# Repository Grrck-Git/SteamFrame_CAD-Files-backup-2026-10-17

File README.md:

# Steam Frame Hardware Reference

> [!WARNING]
> Information provided within this repository is for informational purposes only. The reference material is provided on an AS-IS basis. Valve Corporation reserves the right to change hardware designs in any way. Valve is not responsible for any damage to hardware that may arise from the use of mechanical or electrical interfaces to the Steam Frame that are not "Steam Frame Compatible."  This includes opening or making modifications to the Steam Frame. Content provided in this repository may not be used for commercial purposes. If you wish to pursue a commercial license please reach out to us at steamframecompatible at valvesoftware com.  Please refer to the license.txt document in this repository for all terms and conditions.

This repo contains:
1. Documents for interfacing to the expansion port. **Please read all warnings if designing your own hardware to interface to the expansion port.** This is in the [documents-expansion-port](documents-expansion-port/) folder. 
2. Stripped down CAD of the core module, in the [documents-coremodule](documents-coremodule/) folder.
3. A full USB 3.0 Hub example, built in Altium, found in the [example-expansion-port-full-usb-3.0](example-expansion-port-full-usb-3.0/) folder.
4. A minimal USB 3.0 Hub example, built in KiCad, found in the [example-expansion-port-short-usb](example-expansion-port-short-usb/)
5. Stripped down CAD of the headstrap, in the [documents-headstrap](documents-headstrap/) folder.
6. LED Locations for the controllers in [documents-controller/Steam_Frame_Controller_LED_Locations](documents-controller/Steam_Frame_Controller_LED_Locations.pdf)
7. Controller CAD in [documents-controller](documents-controller)

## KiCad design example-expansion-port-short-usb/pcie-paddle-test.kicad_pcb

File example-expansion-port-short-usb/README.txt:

This is a minimal example for using the expansion port.  We do not recommend using this for a real accessory, because of the rigid connection to the expansion port. But, it is a minimal reference for what could be done to interface with the expansion port.

Could install 1mm headers on top or bottom.

COPPER TOP side FACES USER 

Use:
 * 0.2mm holes
 * 0.1mm outside precision

REQUIREMENTS:
 * ENIG (prefer 2u) or Hard gold pads.
 * 0.8mm total thickness

Custom Notes:
 * You MUST chamfer edge connector.

IF NOT CHAMFERING:
 * 5x3 Panelization
 * Rails All 4 Sides
 * V-Cuts
 * 2mm Spacing between top and bottom.

IF CHAMFERING:
 * 5x2 Panelization
 * Rails All 4 Sides
 * V-Cuts
 * 2mm Spacing between top and bottom.

KiKit Recommended Configuration:
```json
{
    "layout": {
        "alternation": "rows",
        "vspace": "25mm",
        "vbonefirst": "2",
        "rows": "2",
        "cols": "5"
    },
    "cuts": {
        "type": "mousebites"
    },
    "framing": {
        "type": "railslr"
    }
}
```

```
kikit panelize^
    --layout "alternation: rows; vspace: 25mm; hbonefirst: 2; rotation: 180deg; rows: 2; cols: 5" ^
    --tabs "vwidth: 4.7mm; hwidth: 5mm; spacing: 15mm" ^
    --cuts "type: vcuts" ^
    --framing "type: railslr" ^
    "pcie-paddle-test.kicad_pcb" "outd.kicad_pcb"

```

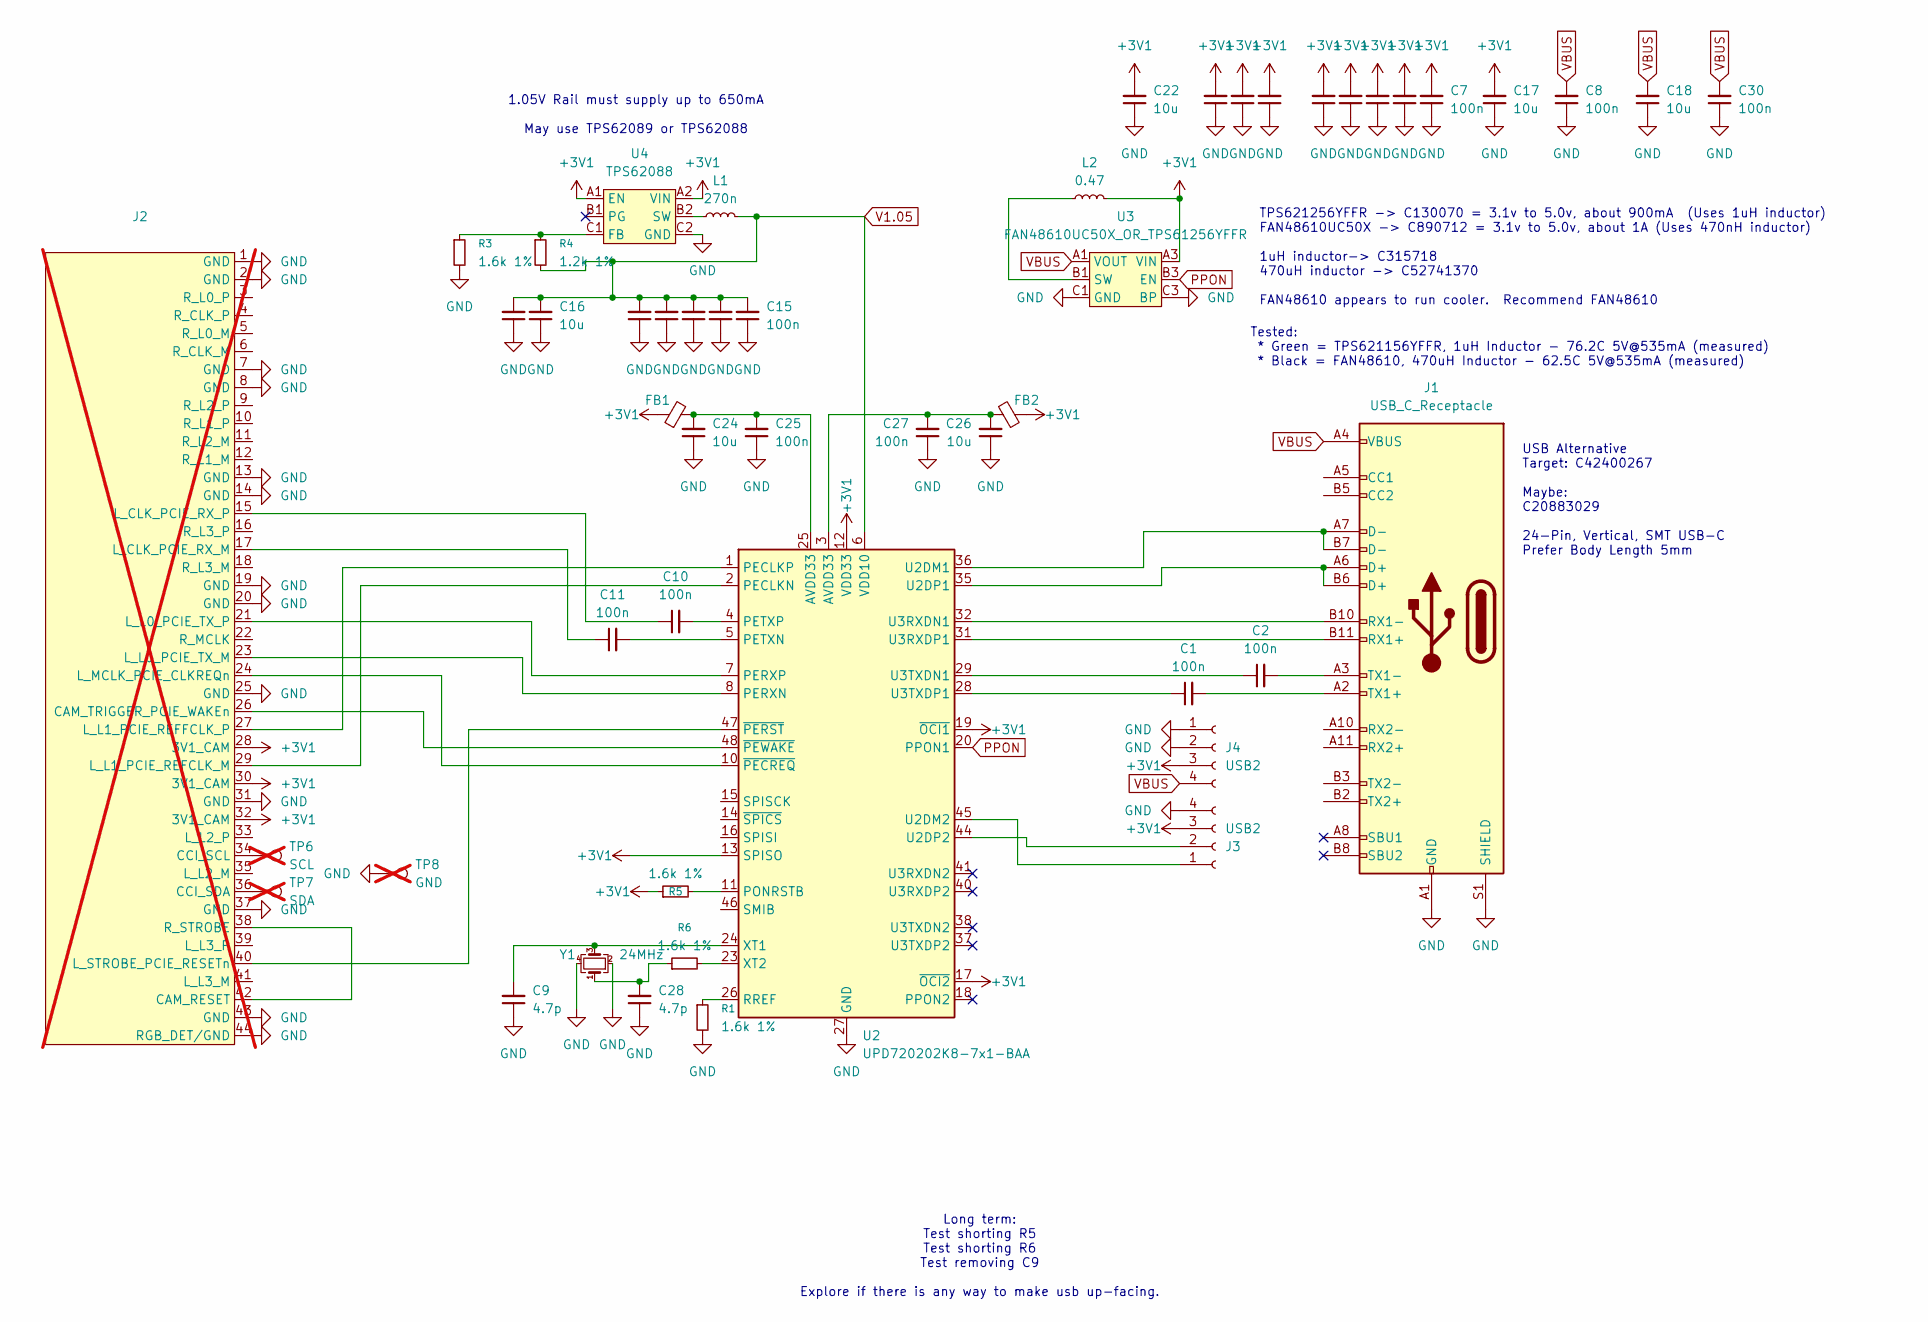
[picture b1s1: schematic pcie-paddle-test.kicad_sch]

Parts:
C1, C2, C3, C4, C5, C6, C7, C8, C10, C11, C12, C13, C14, C15, C19, C20, C23, C25, C27, C29, C30: 100n; C_0201_0603Metric; LCSC C52033358
C9, C28: 4.7p; C_0201_0603Metric; LCSC C255351
C16, C17, C18, C21, C22, C24, C26: 10u; C_0402_1005Metric; LCSC C315248
FB1, FB2: FerriteBead_Small; L_0201_0603Metric; LCSC C710325
J1: USB_C_Receptacle; USB_C_Receptacle_GCT_USB4115-03-C; LCSC C20883029
J2: PCIE-PADDLE-NO-NECK; not fitted
J3, J4: USB2; PinHeader_1x04_P1.00mm_Vertical; LCSC C22465687
L1: 270n; L_0603_1608Metric; LCSC C2041707
L2: 0.47; L_0805_2012Metric; LCSC C52741370
R1, R3, R5, R6: 1.6k 1%; R_0201_0603Metric; LCSC C295784
R4: 1.2k 1%; R_0201_0603Metric; LCSC C327393
TP6: SCL; TestPoint_Pad_D1.0mm; not fitted
TP7: SDA; TestPoint_Pad_D1.0mm; not fitted
TP8: GND; TestPoint_Pad_D1.0mm; not fitted
U2: UPD720202K8-7x1-BAA; QFN-48-1EP_7x7mm_P0.5mm_EP5.7x5.7mm; LCSC C2916548
U3: FAN48610UC50X_OR_TPS61256YFFR; WLP-9_1.468x1.448mm_Layout3x3_P0.4mm; LCSC C890712
U4: TPS62088; Texas_DSBGA-6_0.855x1.255mm_Layout2x3_P0.4mm_LevelB; LCSC C575572
Y1: 24MHz; CRYSTAL-1612; LCSC C2929397

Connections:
+3V1: C3.2, C4.2, C5.2, C6.2, C7.2, C17.2, C19.2, C20.2, C22.2, C29.2, FB1.1, FB2.1, J2.28 (3V1_CAM), J2.30 (3V1_CAM), J2.32 (3V1_CAM), J3.3, J4.3, L2.2, R5.1, U2.12 (VDD33), U2.13 (SPISO), U2.17 (~OCI2), U2.19 (~OCI1), U2.22 (VDD33), U2.34 (VDD33), U2.43 (VDD33), U3.A3 (VIN), U4.A1 (EN), U4.A2 (VIN)
GND: C3.1, C4.1, C5.1, C6.1, C7.1, C8.1, C9.1, C12.1, C13.1, C14.1, C15.1, C16.1, C17.1, C18.1, C19.1, C20.1, C21.1, C22.1, C23.1, C24.1, C25.1, C26.1, C27.1, C28.1, C29.1, C30.1, J1.A1 (GND), J1.A12 (GND), J1.B1 (GND), J1.B12 (GND), J1.S1 (SHIELD), J2.1 (GND), J2.2 (GND), J2.7 (GND), J2.8 (GND), J2.13 (GND), J2.14 (GND), J2.19 (GND), J2.20 (GND), J2.25 (GND), J2.31 (GND), J2.37 (GND), J2.43 (GND), J2.44 (RGB_DET/GND), J3.4, J4.1, J4.2, R1.2, R3.2, TP8.1, U2.27 (GND), U2.49 (GND), U3.C1 (GND), U3.C2 (GND), U3.C3 (BP), U4.C2 (GND), Y1.2, Y1.4
unnamed: C24.2, C25.2, FB1.2, U2.25 (AVDD33)
unnamed: C26.2, C27.2, FB2.2, U2.3 (AVDD33)
unnamed: C28.2, R6.1, Y1.1
unnamed: J1.B11 (RX1+), U2.31 (U3RXDP1)
unnamed: J1.B10 (RX1-), U2.32 (U3RXDN1)
unnamed: C1.2, J1.A2 (TX1+)
unnamed: C2.2, J1.A3 (TX1-)
unnamed: J2.38 (R_STROBE), J2.42 (CAM_RESET)
unnamed: J2.26 (CAM_TRIGGER_PCIE_WAKEn), U2.48 (~PEWAKE)
unnamed: J2.34 (CCI_SCL), TP6.1
unnamed: J2.36 (CCI_SDA), TP7.1
unnamed: C11.1, J2.17 (L_CLK_PCIE_RX_M)
unnamed: C10.1, J2.15 (L_CLK_PCIE_RX_P)
unnamed: J2.23 (L_L0_PCIE_TX_M), U2.8 (PERXN)
unnamed: J2.21 (L_L0_PCIE_TX_P), U2.7 (PERXP)
unnamed: J2.29 (L_L1_PCIE_REFCLK_M), U2.2 (PECLKN)
unnamed: J2.27 (L_L1_PCIE_REFFCLK_P), U2.1 (PECLKP)
unnamed: J2.24 (L_MCLK_PCIE_CLKREQn), U2.10 (~PECREQ)
unnamed: J2.40 (L_STROBE_PCIE_RESETn), U2.47 (~PERST)
unnamed: J3.1, U2.45 (U2DM2)
unnamed: J3.2, U2.44 (U2DP2)
unnamed: L2.1, U3.B1 (SW), U3.B2 (SW)
unnamed: C11.2, U2.5 (PETXN)
unnamed: C10.2, U2.4 (PETXP)
unnamed: R5.2, U2.11 (PONRSTB)
unnamed: R1.1, U2.26 (RREF)
unnamed: J1.A7 (D-), J1.B7 (D-), U2.36 (U2DM1)
unnamed: J1.A6 (D+), J1.B6 (D+), U2.35 (U2DP1)
unnamed: C2.1, U2.29 (U3TXDN1)
unnamed: C1.1, U2.28 (U3TXDP1)
unnamed: C9.2, U2.24 (XT1), Y1.3
unnamed: R6.2, U2.23 (XT2)
unnamed: R3.1, R4.1, U4.C1 (FB)
unnamed: L1.1, U4.B2 (SW)
PPON: U2.20 (PPON1), U3.B3 (EN)
V1.05: C12.2, C13.2, C14.2, C15.2, C16.2, C21.2, C23.2, L1.2, R4.2, U2.6 (VDD10), U2.9 (VDD10), U2.21 (VDD10), U2.30 (VDD10), U2.33 (VDD10), U2.39 (VDD10), U2.42 (VDD10)
VBUS: C8.2, C18.2, C30.2, J1.A4 (VBUS), J1.A9 (VBUS), J1.B4 (VBUS), J1.B9 (VBUS), J4.4, U3.A1 (VOUT), U3.A2 (VOUT)

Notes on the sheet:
Tested: * Green = TPS621156YFFR, 1uH Inductor - 76.2C 5V@535mA (measured) * Black = FAN48610, 470uH Inductor - 62.5C 5V@535mA (measured)
1.05V Rail must supply up to 650mA May use TPS62089 or TPS62088
Long term: Test shorting R5 Test shorting R6 Test removing C9 Explore if there is any way to make usb up-facing.
USB Alternative Target: C42400267 Maybe: C20883029 24-Pin, Vertical, SMT USB-C Prefer Body Length 5mm
TPS621256YFFR -> C130070 = 3.1v to 5.0v, about 900mA (Uses 1uH inductor) FAN48610UC50X -> C890712 = 3.1v to 5.0v, about 1A (Uses 470nH inductor) 1uH inductor-> C315718 470uH inductor -> C52741370 FAN48610 appears to run cooler. Recommend FAN48610

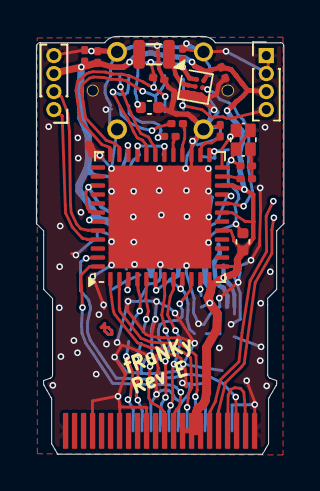
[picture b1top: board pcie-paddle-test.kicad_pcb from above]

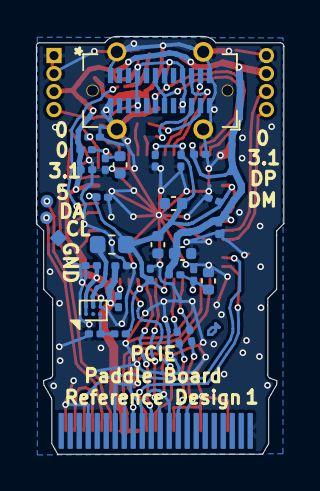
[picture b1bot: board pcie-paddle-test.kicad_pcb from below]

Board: 2 copper layers, 13.7 x 23.2 mm, 50 parts (31 on the bottom side), 39 nets.
